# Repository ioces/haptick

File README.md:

# Haptick - a 6DOF force sensitive input device

This design is a work in progress and is currently in the proof-of-concept prototyping phase. Progress is being documented via a series of [blog posts](https://blog.ioces.com/matt).

Ultimately the goal is to produce an open source alternative to the various [Spacemice](http://spacemice.org/index.php?title=Main_Page) on the market.

## License

This project is licensed under two separate licenses. The hardware design and documentation for this project is licensed under the [CERN Open Hardware Licence Version 2 - Strongly Reciprocal](https://ohwr.org/cern_ohl_s_v2.txt) (CERN-OHL-S-2.0). The software and firmware source code for the project is licensed under the [GNU General Public License Version 3](https://www.gnu.org/licenses/gpl-3.0.txt) (GPL-3.0-only).

Further details can be found in the [license file](LICENSE.md).

### Third Party Libraries

Various third party libraries are used in this project. These libraries are licensed separately from the Haptick project.

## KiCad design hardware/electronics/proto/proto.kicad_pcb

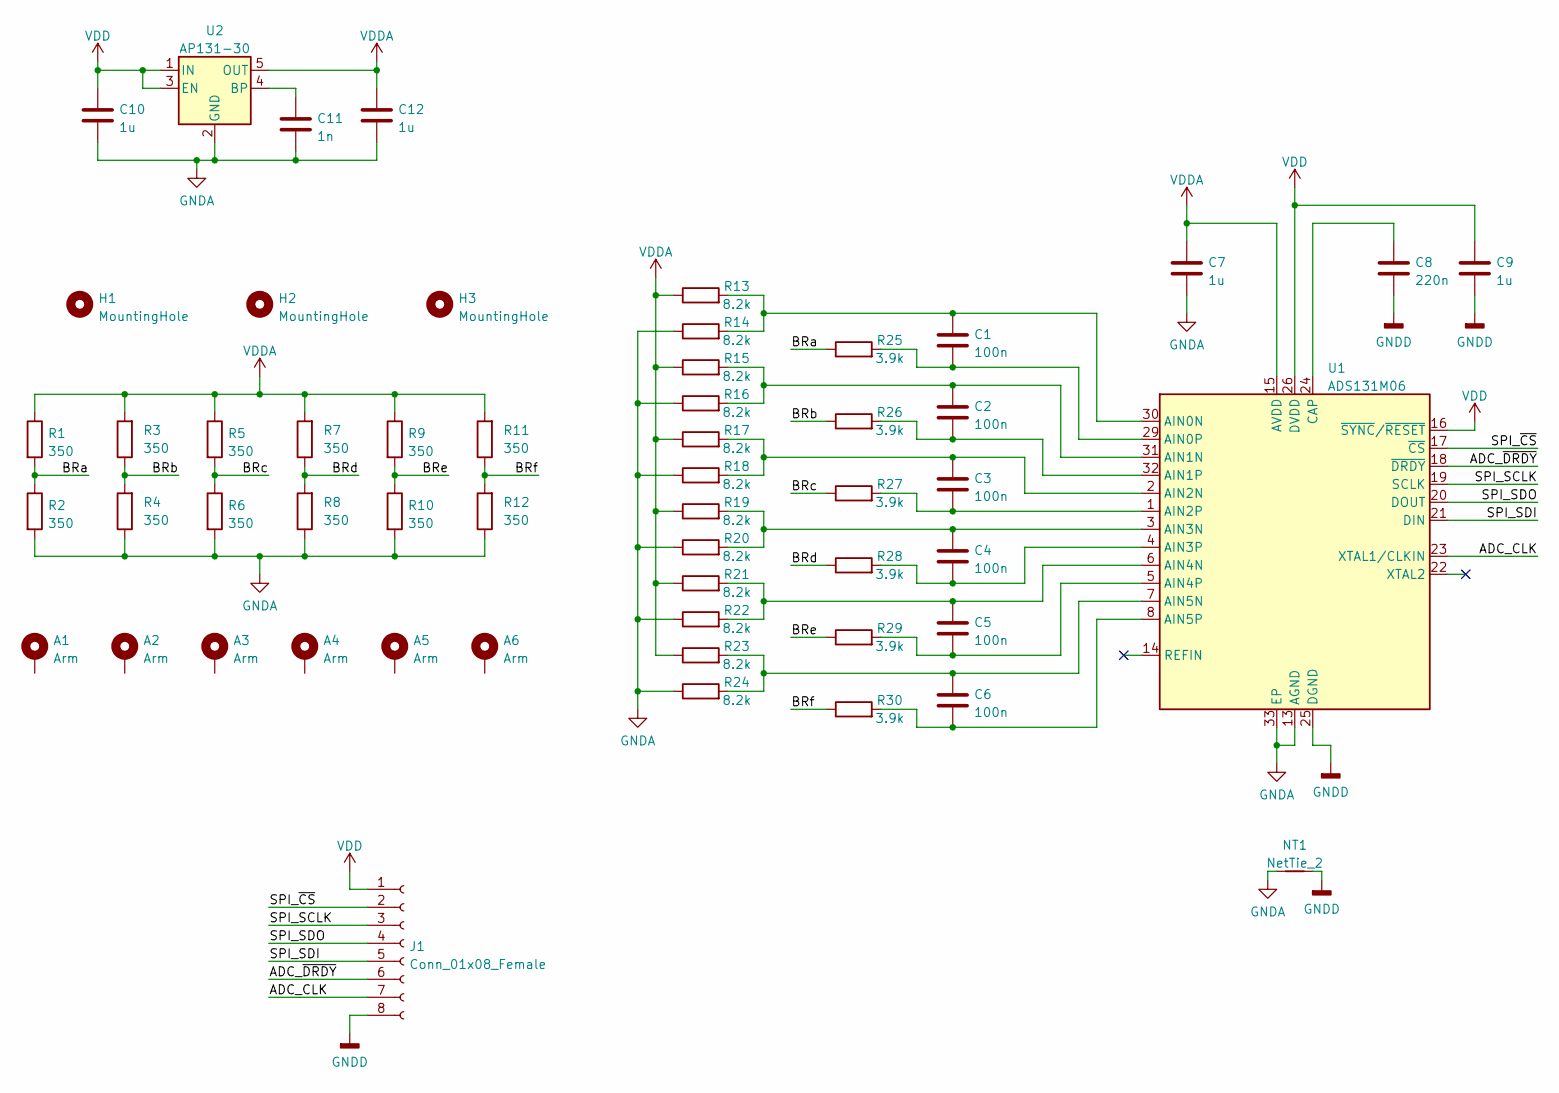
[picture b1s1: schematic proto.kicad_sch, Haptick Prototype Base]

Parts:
A1, A2, A3, A4, A5, A6: Arm; ArmPad
C1, C2, C3, C4, C5, C6: 100n; C_0603_1608Metric_Pad1.08x0.95mm_HandSolder; Part Number CL10B104KB8WPNC
C7, C9, C10, C12: 1u; C_0603_1608Metric_Pad1.08x0.95mm_HandSolder; Part Number CL10B105KA8NNNL
C8: 220n; C_0603_1608Metric_Pad1.08x0.95mm_HandSolder; Part Number CL10B224KO8NFNC
C11: 1n; C_0603_1608Metric_Pad1.08x0.95mm_HandSolder; Part Number CL10B102KB8WPNC
H1, H2, H3: MountingHole; MountingHole_3.2mm_M3
J1: Conn_01x08_Female; TE_2328702-8_1x08-1MP_P0.5mm_Horizontal; Part Number 2328702-8
NT1: NetTie_2; NetTie-2_SMD_Pad0.2mm
R1, R2, R3, R4, R5, R6, R7, R8, R9, R10, R11, R12: 350; StrainGauge_BF350-3AA; Part Number CRGCQ2512F1K0
R13, R14, R15, R16, R17, R18, R19, R20, R21, R22, R23, R24: 8.2k; R_0603_1608Metric_Pad0.98x0.95mm_HandSolder; Part Number RT0603DRD071KL
R25, R26, R27, R28, R29, R30: 3.9k; R_0603_1608Metric_Pad0.98x0.95mm_HandSolder; Part Number RT0603DRD071KL
U1: ADS131M06; QFN-32-1EP_4x4mm_P0.4mm_EP2.9x2.9mm; Part Number ADS131M06IRSNR
U2: AP131-30; SOT-23-5; Part Number TPS7A2030PDBVR

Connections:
/ADC_CLK: J1.7, U1.23 (XTAL1/CLKIN)
/ADC_~DRDY: J1.6, U1.18 (~DRDY)
/BRa: R1.2, R2.1, R25.1
/BRb: R3.1, R4.2, R26.1
/BRc: R5.2, R6.1, R27.1
/BRd: R7.1, R8.2, R28.1
/BRe: R9.2, R10.1, R29.1
/BRf: R11.1, R12.2, R30.1
/SPI_SCLK: J1.3, U1.19 (SCLK)
/SPI_SDI: J1.5, U1.21 (DIN)
/SPI_SDO: J1.4, U1.20 (DOUT)
/SPI_~CS: J1.2, U1.17 (~CS)
GNDA: C7.2, C10.2, C11.2, C12.2, NT1.1, R2.2, R4.1, R6.2, R8.1, R10.2, R12.1, R14.1, R16.1, R18.1, R20.1, R22.1, R24.1, U1.13 (AGND), U1.28 (AGND), U1.33 (EP), U2.2 (GND)
GNDD: C8.2, C9.2, J1.8, NT1.2, U1.25 (DGND)
unnamed: C1.1, R13.2, R14.2, U1.30 (AIN0N)
unnamed: C1.2, R25.2, U1.29 (AIN0P)
unnamed: C2.1, R15.2, R16.2, U1.31 (AIN1N)
unnamed: C2.2, R26.2, U1.32 (AIN1P)
unnamed: C3.1, R17.2, R18.2, U1.2 (AIN2N)
unnamed: C3.2, R27.2, U1.1 (AIN2P)
unnamed: C4.1, R19.2, R20.2, U1.3 (AIN3N)
unnamed: C4.2, R28.2, U1.4 (AIN3P)
unnamed: C5.1, R21.2, R22.2, U1.6 (AIN4N)
unnamed: C5.2, R29.2, U1.5 (AIN4P)
unnamed: C6.1, R23.2, R24.2, U1.7 (AIN5N)
unnamed: C6.2, R30.2, U1.8 (AIN5P)
unnamed: C8.1, U1.24 (CAP)
unnamed: C11.1, U2.4 (BP)
VDD: C9.1, C10.1, J1.1, U1.16 (~SYNC/~RESET), U1.26 (DVDD), U2.1 (IN), U2.3 (EN)
VDDA: C7.1, C12.1, R1.1, R3.2, R5.1, R7.2, R9.1, R11.2, R13.1, R15.1, R17.1, R19.1, R21.1, R23.1, U1.15 (AVDD), U2.5 (OUT)

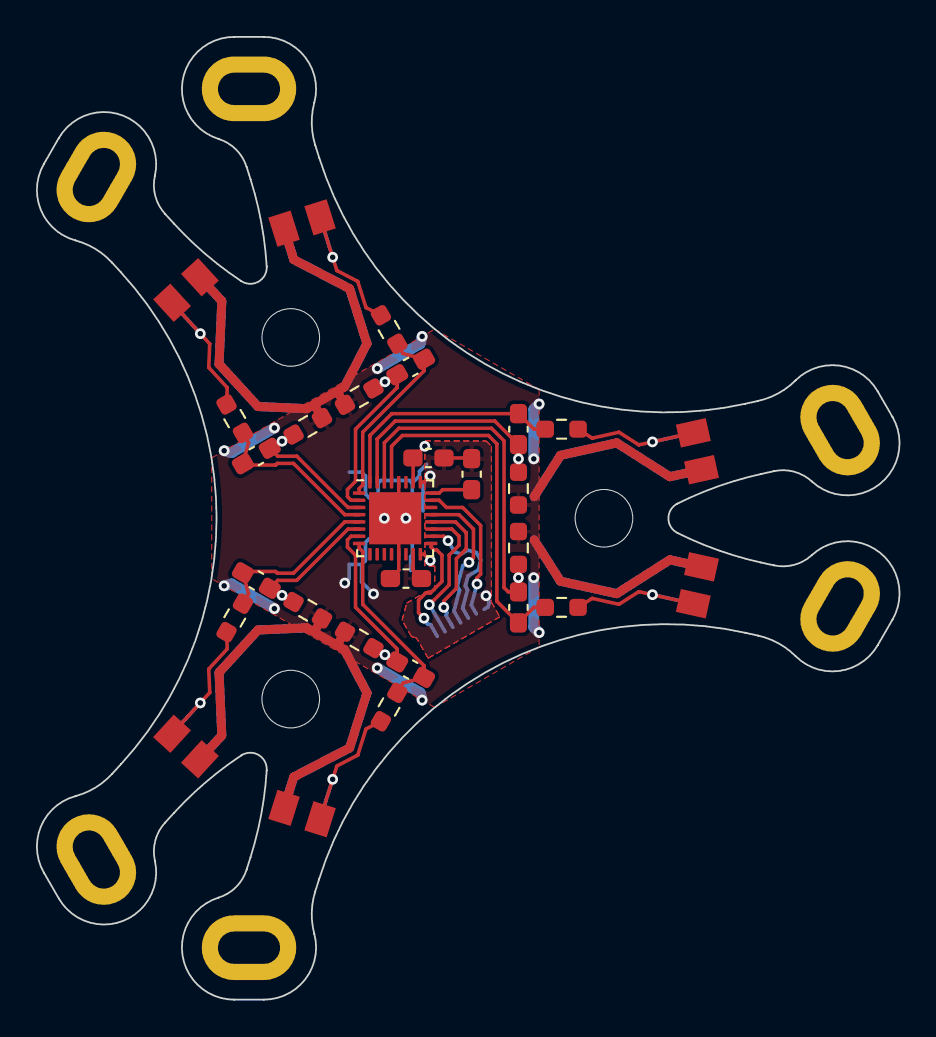
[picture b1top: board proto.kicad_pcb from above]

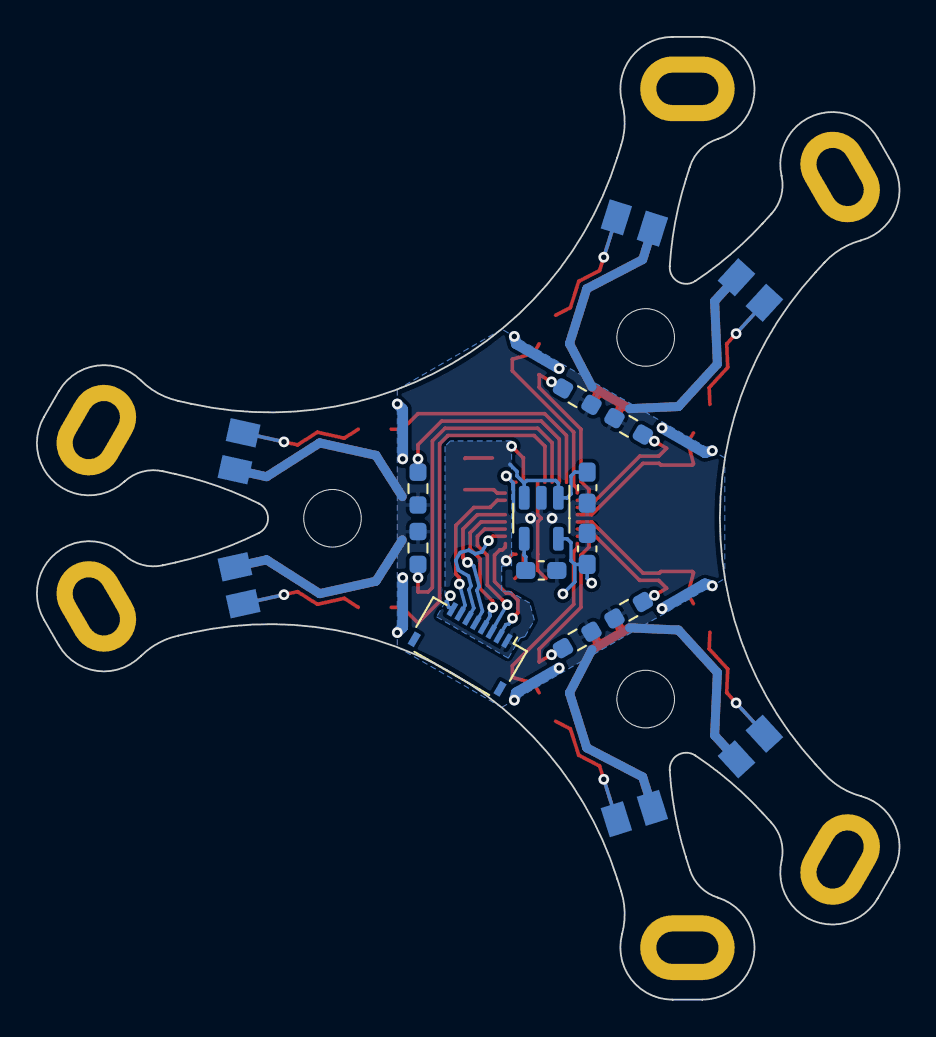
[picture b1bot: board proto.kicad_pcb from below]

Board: 2 copper layers, 47.9 x 53.5 mm, 55 parts (21 on the bottom side), 30 nets.

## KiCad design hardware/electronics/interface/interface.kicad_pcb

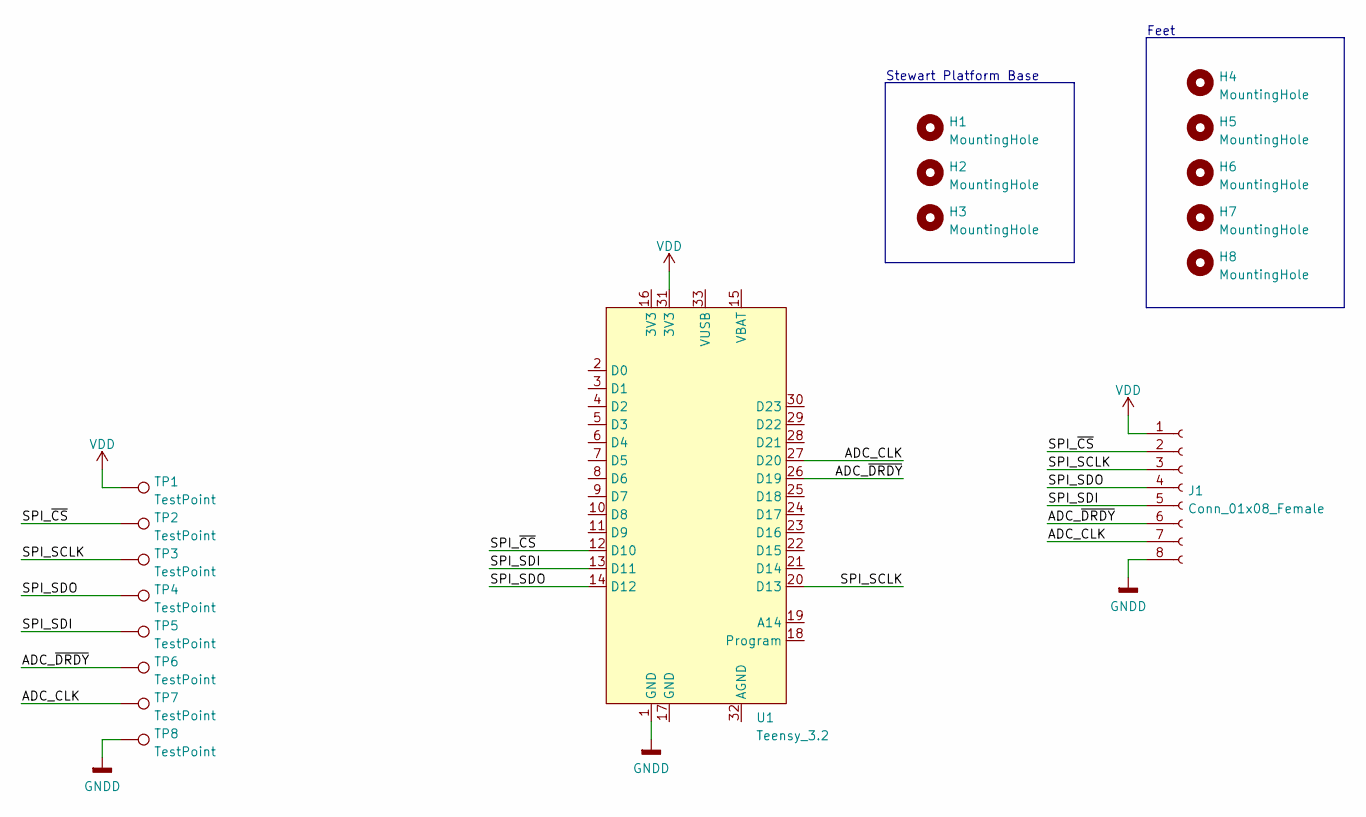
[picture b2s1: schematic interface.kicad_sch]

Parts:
H1, H2, H3: MountingHole; MountingHole_PEM_M3_Broaching_Nut
H4, H5, H6, H7, H8: MountingHole; MountingHole_4.5mm
J1: Conn_01x08_Female; TE_2328702-8_1x08-1MP_P0.5mm_Horizontal
TP1, TP2, TP3, TP4, TP5, TP6, TP7, TP8: TestPoint; TestPoint_THTPad_D1.6mm_Drill0.9mm
U1: Teensy_3.2

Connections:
/ADC_CLK: J1.7, TP7.1, U1.27 (D20)
/ADC_~DRDY: J1.6, TP6.1, U1.26 (D19)
/SPI_SCLK: J1.3, TP3.1, U1.20 (D13)
/SPI_SDI: J1.5, TP5.1, U1.13 (D11)
/SPI_SDO: J1.4, TP4.1, U1.14 (D12)
/SPI_~CS: J1.2, TP2.1, U1.12 (D10)
GNDD: J1.8, TP8.1, U1.1 (GND)
VDD: J1.1, TP1.1, U1.31 (3V3)

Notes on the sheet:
Feet
Stewart Platform Base

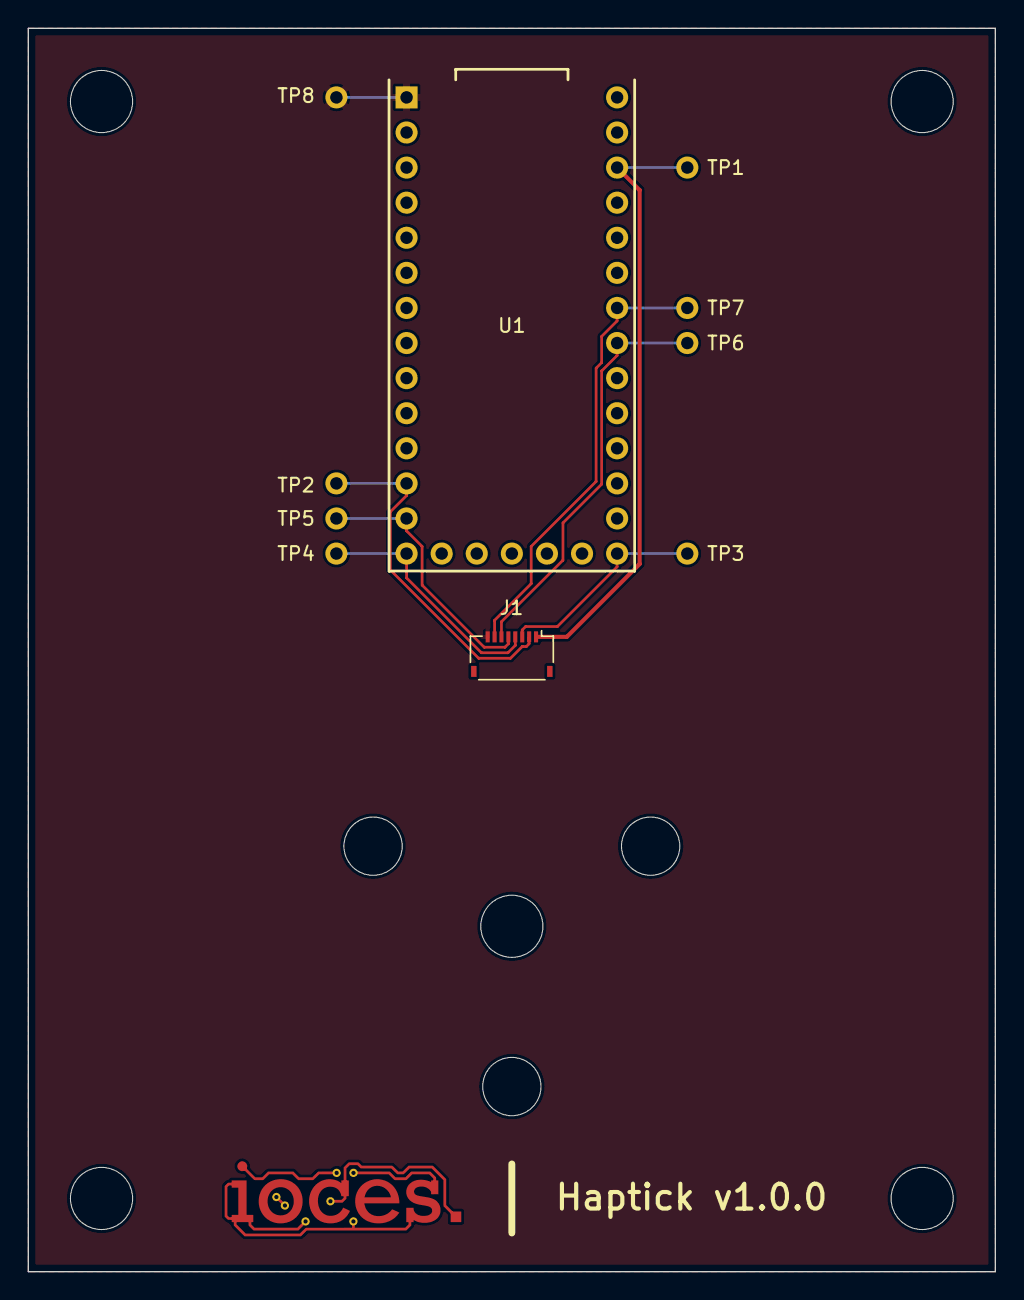
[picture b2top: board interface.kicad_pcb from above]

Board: 2 copper layers, 70.0 x 90.0 mm, 19 parts (0 on the bottom side), 8 nets.

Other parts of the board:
Ref**: Val**; IocesLogo

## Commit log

2022-12-04 Fix order of cleanup on close/disconnect
2022-12-10 Move firmware file and use flag to put writes in main loop
2022-12-10 Handle the case where there is no connection on disconnection
2022-12-10 Add a PSD plot
2022-12-10 Don't downsample data
2022-12-10 Add some more sensible defaults for the PSD plot
2022-12-10 No point in joining if there is no connection
2022-12-10 Abstract out Matplotlib canvas
2022-12-10 Add tabs for both voltage and PSD plots
2022-12-10 Disable filter by default
2022-12-10 Allow setting of the filter cutoff
2022-12-10 Add a power spectral density plot (#1)
2022-12-10 Add a widget displaying RMS noise of the 6 channels
2022-12-11 Add a widget displaying RMS noise of the 6 channels (#3)
2022-12-11 Calculate forces and torques from truss force magnitudes
2022-12-14 Start on an OpenGL based force/torque display
2022-12-15 Start blindly trying to write some OpenGL code
2022-12-20 Drew a cube!
2022-12-22 Round the cube, add some texture
2022-12-23 Updated texture and lighting to look nicer
2022-12-23 Do translation and rotation based on Haptick input
2022-12-24 Make force/torque inputs affect translational/rotational velocity
2022-12-24 Calculate and display position/rotation from input forces and torques (#4)
2022-12-26 Try some really basic continual bias correction
2022-12-26 Bump up rotation sensitivity a bit
2022-12-26 Formatting fixes and add some comments
2022-12-26 Wait for the serial port to come up before starting to deal with the ADC data
2022-12-26 Improve reliability of the prototype serial connection (#2)
2022-12-31 Start working on a configurable cube control
2022-12-31 Well, the cube is flying off the screen now.
2022-12-31 Set default slider positions
2022-12-31 Handle NaNs in the visualisers
2022-12-31 Rudimentary bias correction
2022-12-31 Allow changing sensitivities
2023-01-01 Make rotations and translations relative to the camera view
2023-01-03 Start working on some bias correction settings
2023-01-05 Apply bias correction when valid
2023-01-05 Simplify a little
2023-01-06 Start hooking up bias correction settings
2023-01-08 Actually set bias correction settings when UI changes
2023-01-10 Add settings and control to cube motion playground (#7)
2023-01-10 Switch strain gauge footprints
2023-01-12 Finish BF350-3AA footprint based on high res photos
2023-01-12 Update resistor values and add series R for better RC filtering
2023-01-12 Update layout and route
2023-01-12 Use strain gauges instead of thick film resistors (#8)
2023-01-13 Move prototype base PCB into center of sheet
2023-01-13 Bump version of prototype base schematics and layout
2023-01-13 Prepare for release of new prototype (#9)
2023-01-14 Rebuild zones and generate Gerbers for prototype base
2023-02-25 Update manufacturers and part numbers for new prototype
2023-02-25 Update manufacturers and part numbers for new prototype (#10)
2023-03-24 Add a record button
2023-03-26 Update some license information
2023-03-27 Split poll and update timers, handle long value updates and switch to Qt assets
2023-03-27 Back to 50 fps
2023-03-27 Handle loading textures when running from another directory
2023-03-29 Push buffering back to the subprocess side of the Haptick interface
2023-04-01 Save a CSV when recording
2023-04-01 Forgot to disconnect a slot
2023-04-01 Bias cache samples were not in the right order
2023-04-01 Slow things down a bit
2023-04-01 Ignore resources
2023-04-01 Stop button resizing when replacing icon
2023-04-01 Add the ability to record data (#12)
2023-04-01 Delay startup of SPI and configuration setting
    This is necessary on the latest prototype. I think the ADC is taking a little while to come up, and is missing the configuration sent to it without the delay.
2023-04-01 Delay startup of SPI and configuration setting (#13)
    This is necessary on the latest prototype. I think the ADC is taking a little while to come up, and is missing the configuration sent to it without the delay.
